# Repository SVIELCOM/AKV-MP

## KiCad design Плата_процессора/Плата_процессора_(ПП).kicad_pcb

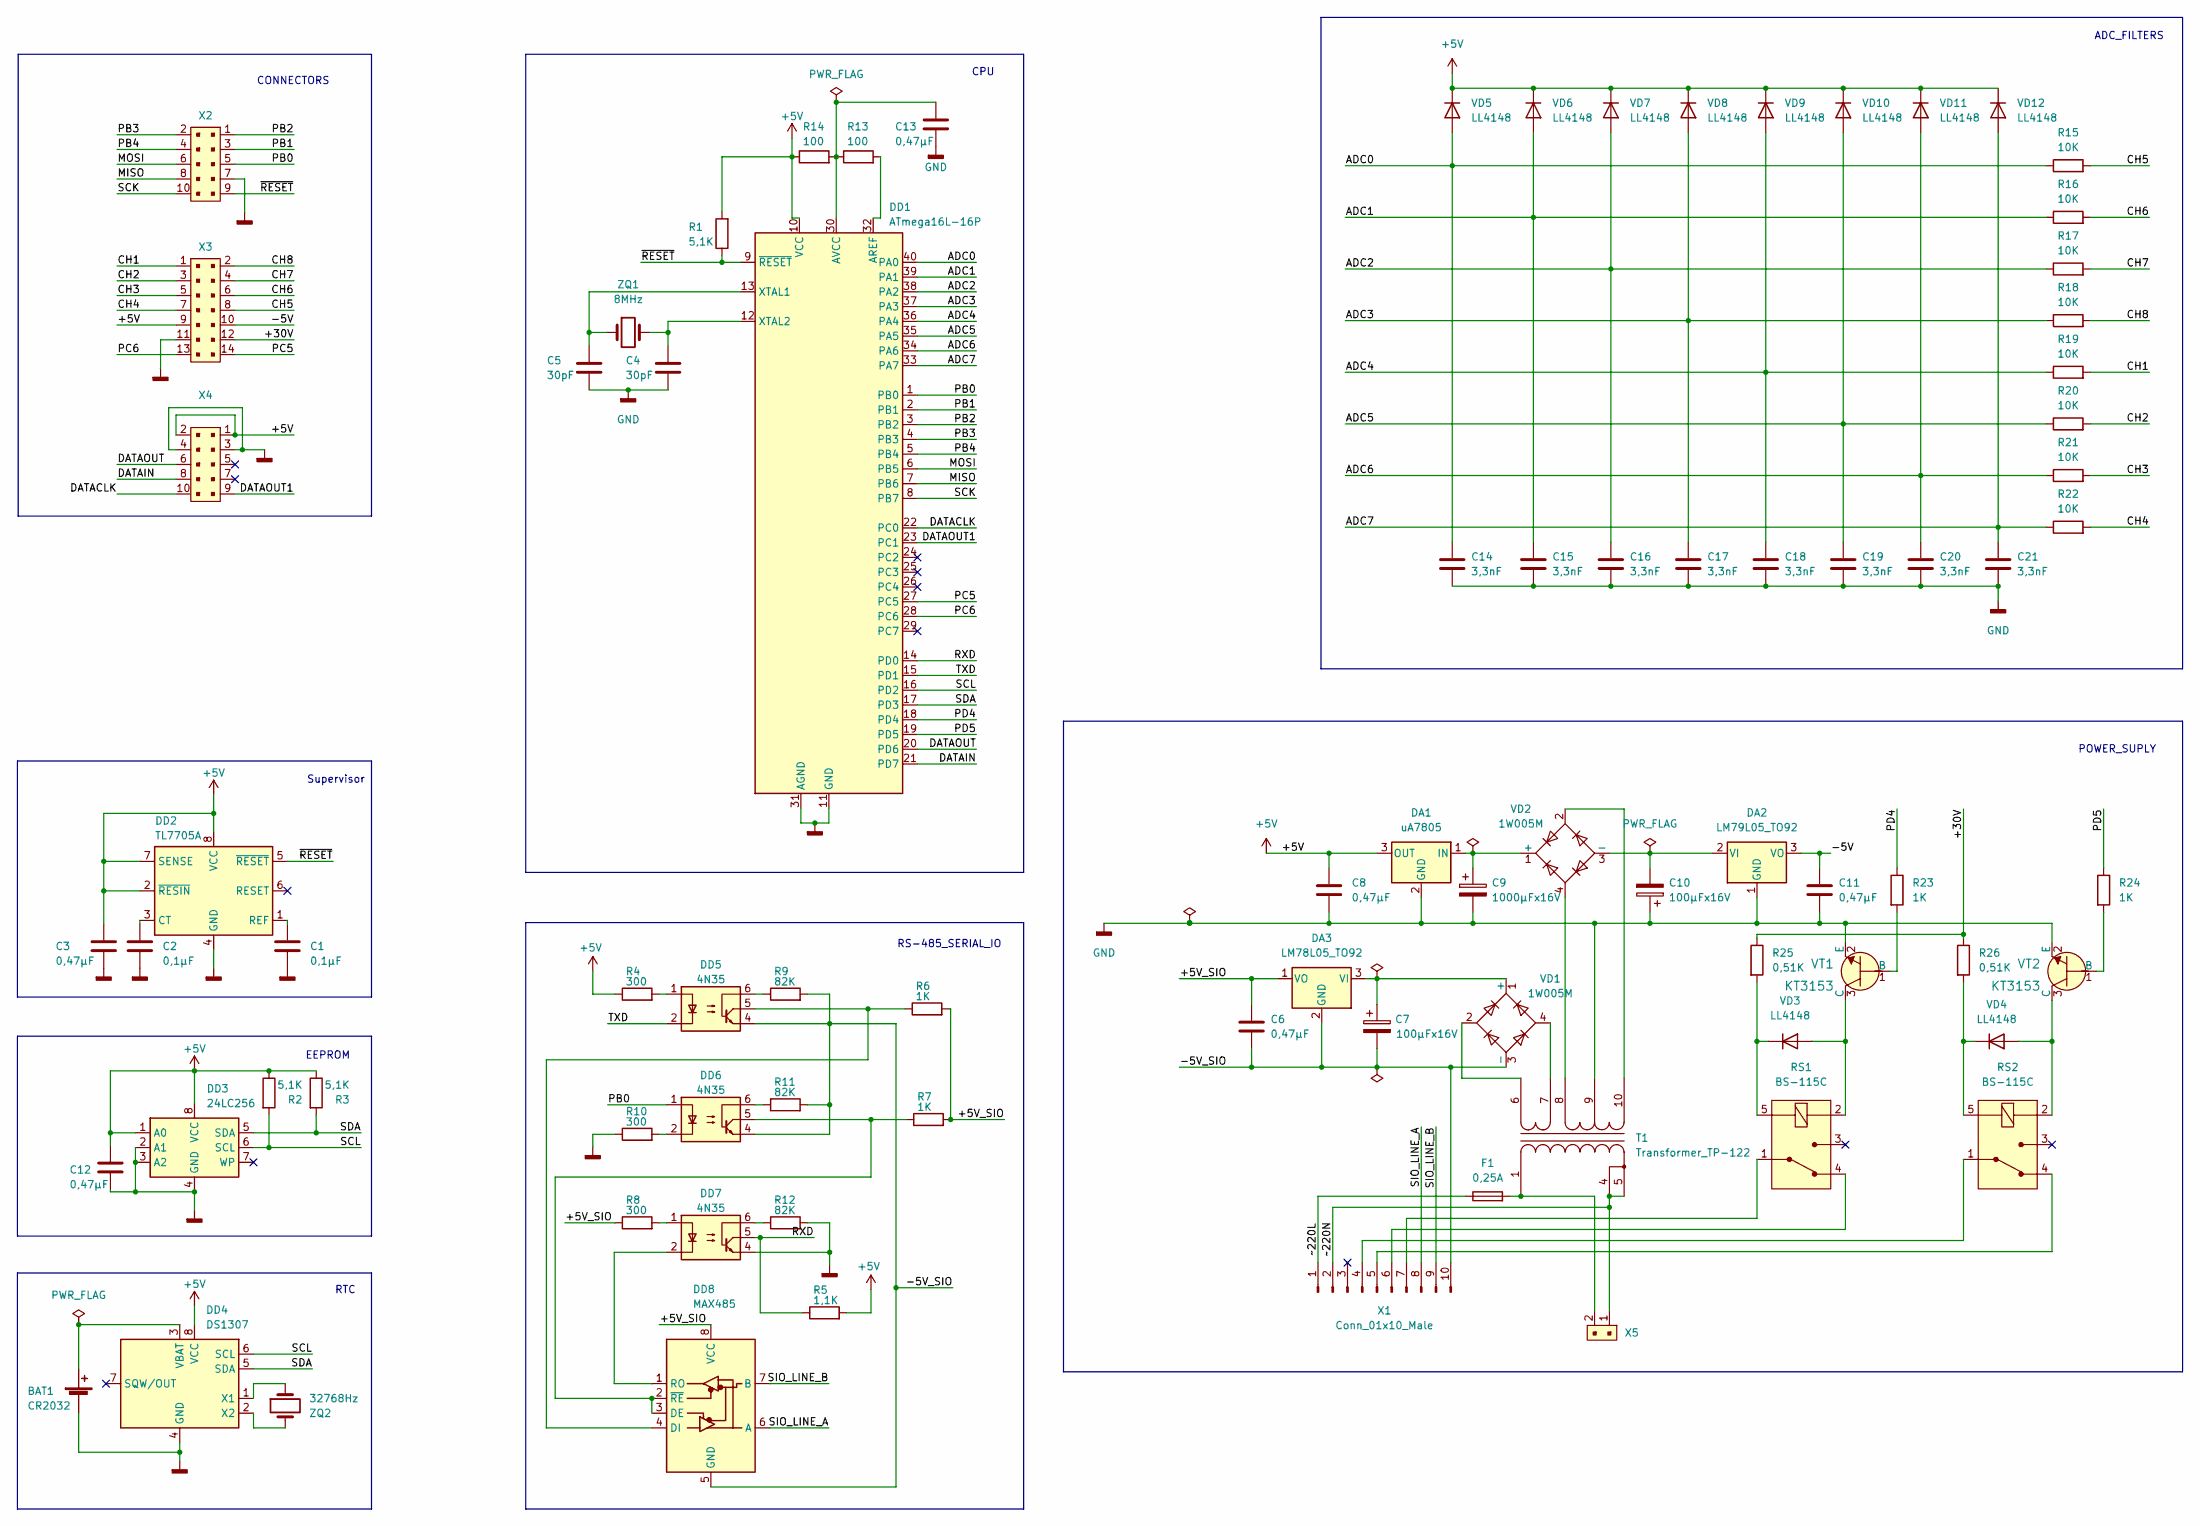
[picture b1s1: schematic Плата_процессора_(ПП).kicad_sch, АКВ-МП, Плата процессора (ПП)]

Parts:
BAT1: CR2032; BAT_BS-7
C1, C2: 0,1µF; C_Disc_D4.7mm_W2.5mm_P5.00mm
C3, C6, C8, C11, C12, C13: 0,47µF; C_1206_3216Metric
C4, C5: 30pF; C_1206_3216Metric
C7, C10: 100µFx16V; CP_Radial_D6.3mm_P2.50mm
C9: 1000µFx16V; CP_Radial_D10.0mm_P5.00mm
C14, C15, C16, C17, C18, C19, C20, C21: 3,3nF; C_1206_3216Metric
DA1: uA7805; TO-220-3_Vertical
DA2: LM79L05_TO92; TO-92_Inline
DA3: LM78L05_TO92; TO-92_Inline
DD1: ATmega16L-16P; DIP-40_W15.24mm
DD2: TL7705A; DIP-8_W7.62mm
DD3: 24LC256; DIP-8_W7.62mm
DD4: DS1307; DIP-8_W7.62mm
DD5, DD6, DD7: 4N35; DIP-6_W7.62mm
DD8: MAX485; DIP-8_W7.62mm
F1: 0,25A; Fuse_Littelfuse-LVR100_AKV
R1, R2, R3: 5,1K; R_1206_3216Metric
R4: 300; R_Axial_DIN0207_L6.3mm_D2.5mm_P10.16mm_Horizontal
R5: 1,1К; R_Axial_DIN0207_L6.3mm_D2.5mm_P10.16mm_Horizontal
R6, R7: 1К; R_1206_3216Metric
R8, R10: 300; R_1206_3216Metric
R9, R11, R12: 82К; R_1206_3216Metric
R13, R14: 100; R_1206_3216Metric
R15, R16, R17, R18, R19, R20, R21, R22: 10К; R_Axial_DIN0207_L6.3mm_D2.5mm_P10.16mm_Horizontal
R23, R24: 1К; R_Axial_DIN0411_L9.9mm_D3.6mm_P12.70mm_Horizontal
R25, R26: 0,51К; R_Axial_DIN0207_L6.3mm_D2.5mm_P10.16mm_Horizontal
RS1, RS2: BS-115C; Relay_THT_G5LE-14
T1: Transformer_TP-122
VD1, VD2: 1W005M; Diode_Bridge_Round_D9.0mm
VD3, VD4, VD5, VD6, VD7, VD8, VD9, VD10, VD11, VD12: LL4148; D_MiniMELF
VT1, VT2: KT3153; SOT-23; MPN BC817-25LT1G; Digi-Key_PN BC817-25LT1GOSCT-ND
X1: Conn_01x10_Male; PhoenixContact_MSTB_2,5_10-GF-5,08_1x10_P5.08mm_Horizontal_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
X2, X4: 302-S101; PinHeader_2x5_P2.54mm_Drill1.2mm; MPN 302-S101; Digi-Key_PN ED1543-ND
X3: 0878311420; PinHeader_2x7_P2.54mm_Drill1.2mm; MPN 0878311420; Digi-Key_PN WM17469-ND
X5: 22-23-2021; PhoenixContact_GMSTBA_2,5_2-G-7,62_1x02_P7.62mm_Horizontal; MPN 22-23-2021; Digi-Key_PN WM4200-ND
ZQ1: 8MHz; Crystal_HC18-U_Vertical
ZQ2: 32768Hz; Crystal_C38-LF_D3.0mm_L8.0mm_Vertical

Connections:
+5V: C3.2, C8.1, C12.1, DA1.3 (OUT), DD1.10 (VCC), DD2.2 (~RESIN), DD2.7 (SENSE), DD2.8 (VCC), DD3.1 (A0), DD3.8 (VCC), DD4.8 (VCC), R1.2, R2.1, R3.1, R4.1, R5.2, R14.1, VD5.1 (K), VD6.1 (K), VD7.1 (K), VD8.1 (K), VD9.1 (K), VD10.1 (K), VD11.1 (K), VD12.1 (K), X3.9, X4.1, X4.2
/+5V_SIO: C6.1, DA3.1 (VO), DD8.8 (VCC), R6.2, R7.2, R8.1
/+30V: R25.1, R26.1, X3.12
/-5V: C11.1, DA2.3 (VO), X3.10
/-5V_SIO: C6.2, C7.2, DA3.2 (GND), DD5.4, DD6.4, DD8.5 (GND), R9.2, R11.2, VD1.3 (-), X1.10
/ADC0: C14.1, DD1.40 (PA0), R15.1, VD5.2 (A)
/ADC1: C15.1, DD1.39 (PA1), R16.1, VD6.2 (A)
/ADC2: C16.1, DD1.38 (PA2), R17.1, VD7.2 (A)
/ADC3: C17.1, DD1.37 (PA3), R18.1, VD8.2 (A)
/ADC4: C18.1, DD1.36 (PA4), R19.1, VD9.2 (A)
/ADC5: C19.1, DD1.35 (PA5), R20.1, VD10.2 (A)
/ADC6: C20.1, DD1.34 (PA6), R21.1, VD11.2 (A)
/ADC7: C21.1, DD1.33 (PA7), R22.1, VD12.2 (A)
/CH1: R19.2, X3.1
/CH2: R20.2, X3.3
/CH3: R21.2, X3.5
/CH4: R22.2, X3.7
/CH5: R15.2, X3.8
/CH6: R16.2, X3.6
/CH7: R17.2, X3.4
/CH8: R18.2, X3.2
/DATACLK: DD1.22 (PC0), X4.10
/DATAIN: DD1.21 (PD7), X4.8
/DATAOUT: DD1.20 (PD6), X4.6
/DATAOUT1: DD1.23 (PC1), X4.9
/MISO: DD1.7 (PB6), X2.8
/MOSI: DD1.6 (PB5), X2.6
/PB0: DD1.1 (PB0), DD6.1, X2.5
/PB1: DD1.2 (PB1), X2.3
/PB2: DD1.3 (PB2), X2.1
/PB3: DD1.4 (PB3), X2.2
/PB4: DD1.5 (PB4), X2.4
/PC5: DD1.27 (PC5), X3.14
/PC6: DD1.28 (PC6), X3.13
/PD4: DD1.18 (PD4), R23.1
/PD5: DD1.19 (PD5), R24.1
/RXD: DD1.14 (PD0), DD7.5, R5.1
/SCK: DD1.8 (PB7), X2.10
/SCL: DD1.16 (PD2), DD3.6 (SCL), DD4.6 (SCL), R2.2
/SDA: DD1.17 (PD3), DD3.5 (SDA), DD4.5 (SDA), R3.2
/SIO_LINE_A: DD8.6 (A), X1.8
/SIO_LINE_B: DD8.7 (B), X1.9
/TXD: DD1.15 (PD1), DD5.2
/~220L: F1.1, X1.1
/~220N: T1.4 (AB), T1.5 (AB), X1.2, X5.1
/~RESET: DD1.9 (~RESET), DD2.5 (~RESET), R1.1, X2.9
GNDD: BAT1.2 (-), C1.1, C2.1, C3.1, C4.1, C5.1, C8.2, C9.2, C10.1, C11.2, C12.2, C13.2, C14.2, C15.2, C16.2, C17.2, C18.2, C19.2, C20.2, C21.2, DA1.2 (GND), DA2.1 (GND), DD1.11 (GND), DD1.31 (AGND), DD2.4 (GND), DD3.2 (A1), DD3.3 (A2), DD3.4 (GND), DD4.4 (GND), DD7.4, R10.1, R12.2, T1.9 (SC), VT1.2 (E), VT2.2 (E), X2.7, X3.11, X4.3, X4.4
unnamed: BAT1.1 (+), DD4.3 (VBAT)
unnamed: C1.2, DD2.1 (REF)
unnamed: C2.2, DD2.3 (CT)
unnamed: C4.2, DD1.12 (XTAL2), ZQ1.2
unnamed: C5.2, DD1.13 (XTAL1), ZQ1.1
unnamed: C7.1, DA3.3 (VI), VD1.1 (+)
unnamed: C9.1, DA1.1 (IN), VD2.1 (+)
unnamed: C10.2, DA2.2 (VI), VD2.3 (-)
unnamed: C13.1, DD1.30 (AVCC), R13.1, R14.2
unnamed: DD1.32 (AREF), R13.2
unnamed: DD4.1 (X1), ZQ2.1
unnamed: DD4.2 (X2), ZQ2.2
unnamed: DD5.1, R4.2
unnamed: DD5.5, DD8.4 (DI), R6.1
unnamed: DD5.6, R9.1
unnamed: DD6.2, R10.2
unnamed: DD6.5, DD8.2 (~RE), DD8.3 (DE), R7.1
unnamed: DD6.6, R11.1
unnamed: DD7.1, R8.2
unnamed: DD7.2, DD8.1 (RO)
unnamed: DD7.6, R12.1
unnamed: F1.2, T1.1 (AA), X5.2
unnamed: R23.2, VT1.1 (B)
unnamed: R24.2, VT2.1 (B)
unnamed: R25.2, RS1.5 (COIL), VD3.1 (K)
unnamed: R26.2, RS2.5 (COIL), VD4.1 (K)
unnamed: RS1.1 (COM), X1.7
unnamed: RS1.2 (COIL), VD3.2 (A), VT1.3 (C)
unnamed: RS1.4 (NC), X1.6
unnamed: RS2.1 (COM), X1.4
unnamed: RS2.2 (COIL), VD4.2 (A), VT2.3 (C)
unnamed: RS2.4 (NC), X1.5
unnamed: T1.6 (AA), VD1.2
unnamed: T1.7 (AA), VD1.4
unnamed: T1.8 (SB), VD2.4
unnamed: T1.10 (SA), VD2.2

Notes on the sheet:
Supervisor
RTC
RS-485_SERIAL_IO
CPU
EEPROM
CONNECTORS
ADC_FILTERS
POWER_SUPLY

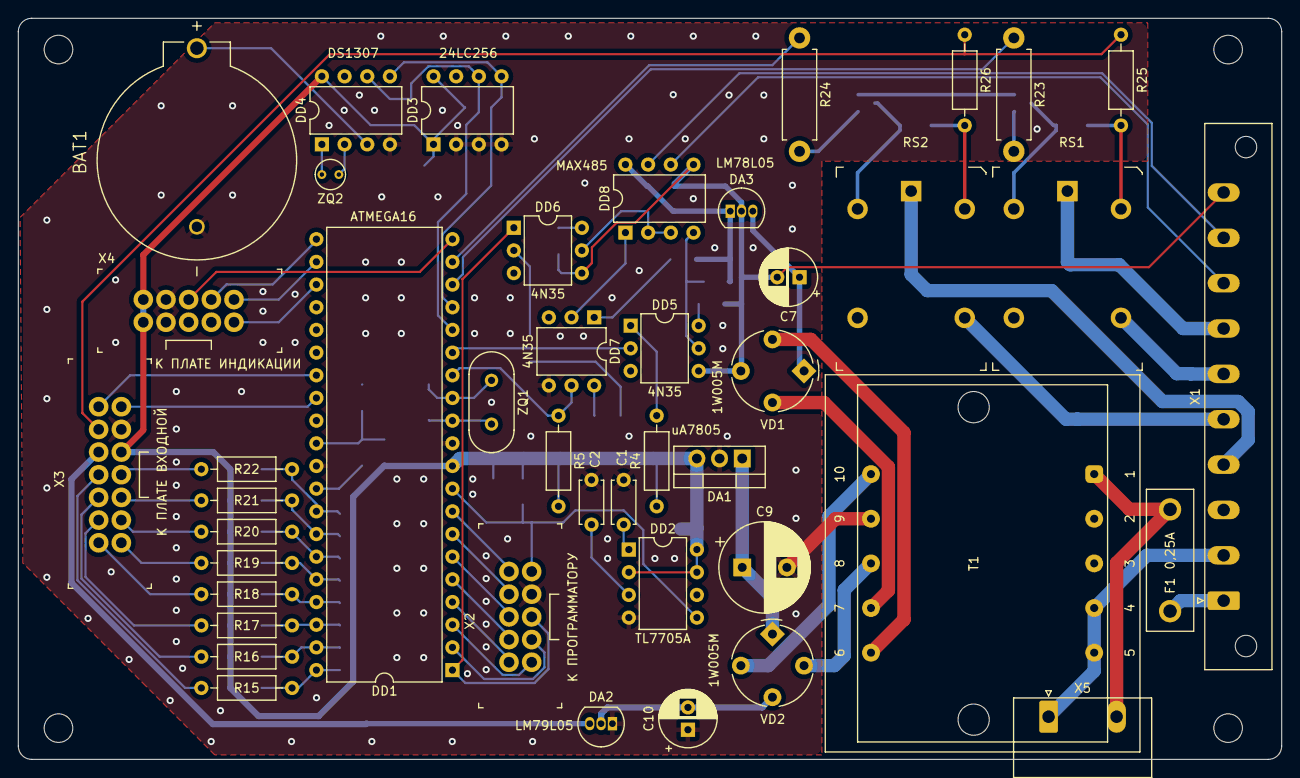
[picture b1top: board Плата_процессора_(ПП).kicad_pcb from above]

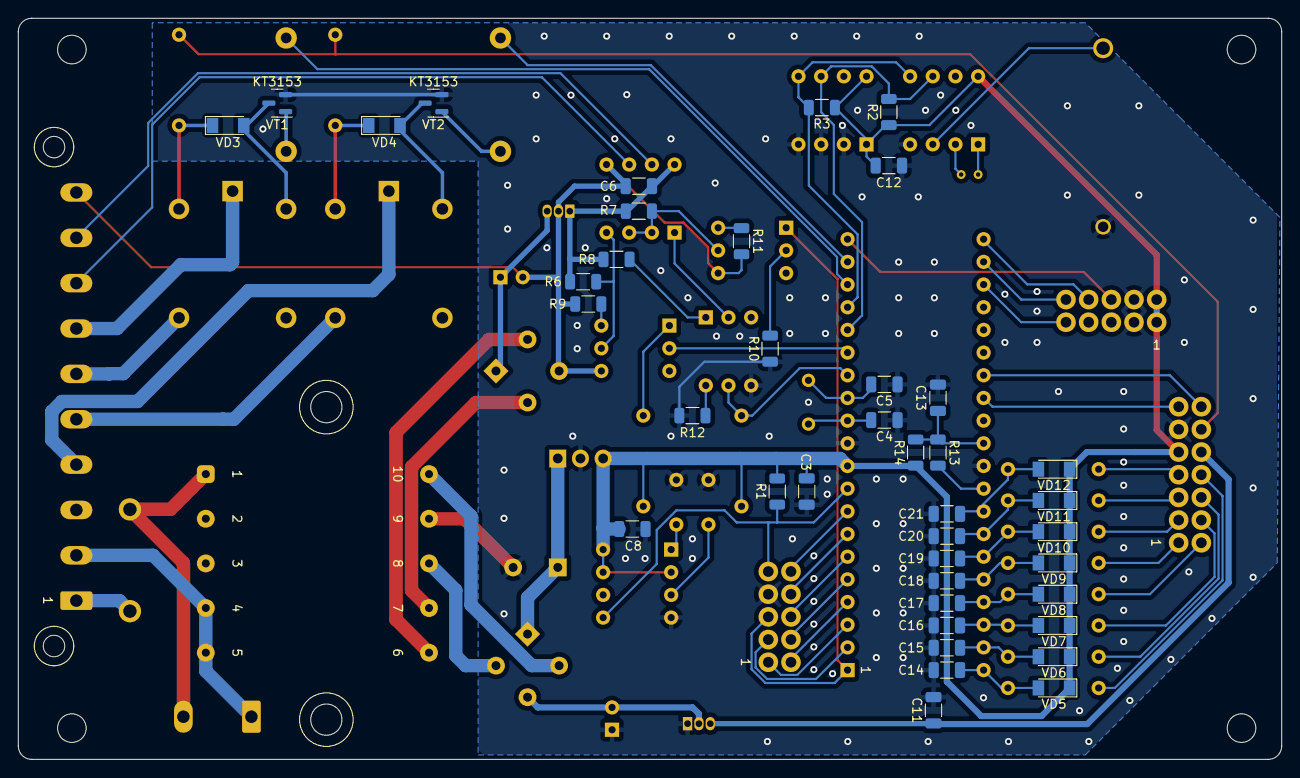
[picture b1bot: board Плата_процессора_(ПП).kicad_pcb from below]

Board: 2 copper layers, 141.5 x 83.0 mm, 84 parts (40 on the bottom side), 83 nets.

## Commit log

2022-07-28 Готовая плата процессора
2022-07-28 folder and file refactoring
